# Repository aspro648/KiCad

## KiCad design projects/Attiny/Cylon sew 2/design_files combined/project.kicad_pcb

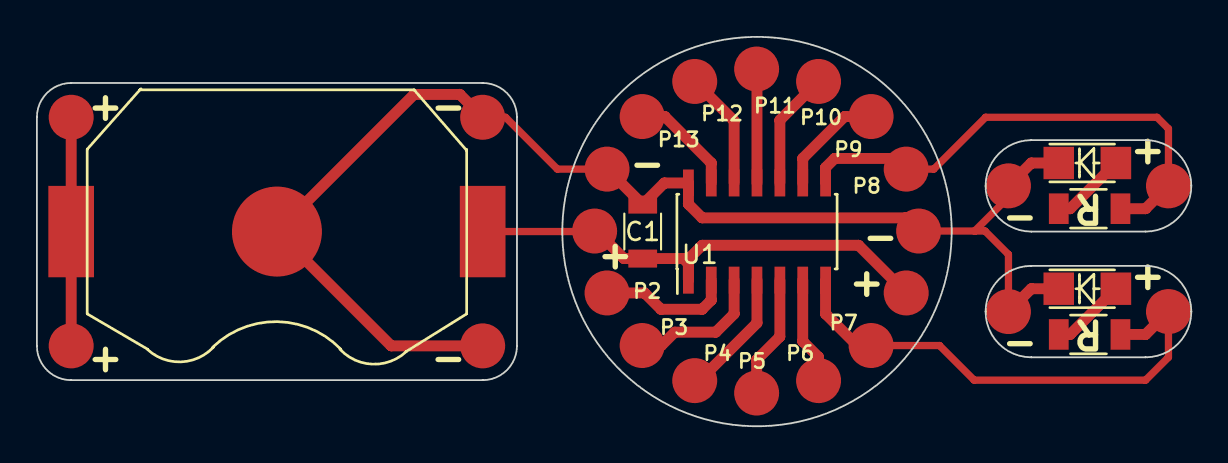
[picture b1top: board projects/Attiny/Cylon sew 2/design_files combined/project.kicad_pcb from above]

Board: 2 copper layers, 64.1 x 21.6 mm, 31 parts (0 on the bottom side), 16 nets.

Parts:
BT1: Battery; BATT_CR2032_SMD
C1: 0.1 uF; C_1206
D5, D5#2: LED; LED-1206
P1, P2, P3, P4, P5, P6, P7, P8, P8#2, P8#3, P9, P10, P11, P12, P13, P14, P14#2, P14#3: CONN_01X01; Pad
PG1, PG1#2, PG2: CONN_01X01; Pad
PP1, PP1#2, PP2: CONN_01X01; Pad
R5, R5#2: 100; R_1206
U1: ATTINY84A-SSU; SOIC-14_3.9x8.7mm_Pitch1.27mm

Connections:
+BATT: BT1.1, C1.1, P1.1, PP1.1, PP1#2.1, PP2.1, U1.1
/D0: P2.1, U1.2
/D1: P3.1, U1.3
/D2: P5.1, U1.5
/D3: P6.1, U1.6
/D4-MOSI: P7.1, P8#3.1, R5#2.1, U1.7
/D5-MISO: P8.1, P8#2.1, R5.1, U1.8
/D6-SCK: P9.1, U1.9
/D7: P10.1, U1.10
/D8: P11.1, U1.11
/D9: P12.1, U1.12
/D10: P13.1, U1.13
/RESET: P4.1, U1.4
GND: BT1.2, C1.2, D5.1, D5#2.1, P14.1, P14#2.1, P14#3.1, PG1.1, PG1#2.1, PG2.1, U1.14
unnamed: D5.2, R5.2
unnamed: D5#2.2, R5#2.2

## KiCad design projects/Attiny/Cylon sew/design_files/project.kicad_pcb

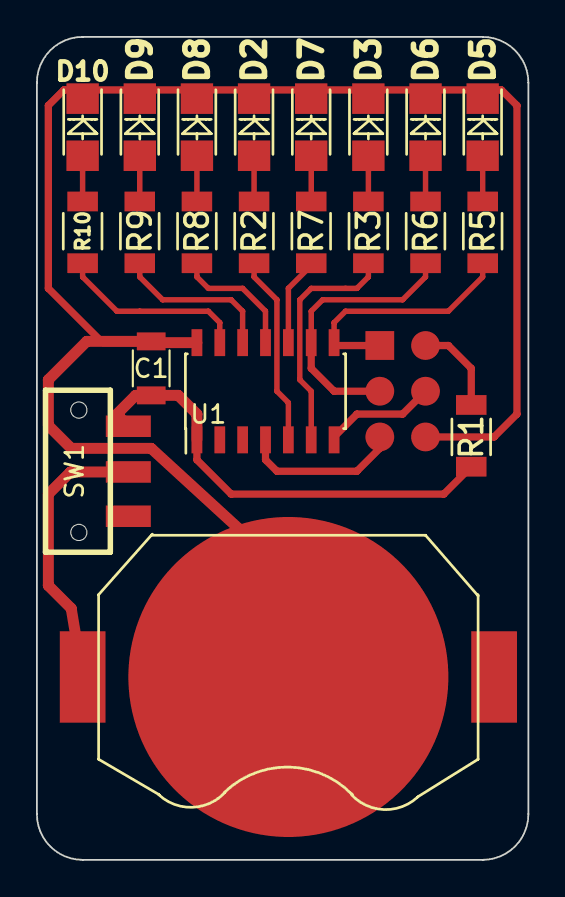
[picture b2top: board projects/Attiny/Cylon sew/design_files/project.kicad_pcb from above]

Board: 2 copper layers, 27.3 x 45.7 mm, 22 parts (0 on the bottom side), 22 nets.

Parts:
BT1: Battery; BATT_CR2032_SMD
C1: 0.1 uF; C_1206
CON1: AVR-ISP-6
D2, D3, D5, D6, D7, D8, D9, D10: LED; LED-1206
R1: 0; R_1206
R2, R3, R5, R6, R7, R8, R9, R10: 100; R_1206
SW1: SW_SPDT; SPST_SMD
U1: ATTINY84A-SSU; SOIC-14_3.9x8.7mm_Pitch1.27mm

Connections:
+BATT: C1.1, R1.2, SW1.3, U1.1
/D2: R2.1, U1.5
/D3: R3.1, U1.6
/D4-MOSI: CON1.4, U1.7
/D5-MISO: CON1.1, R5.1, U1.8
/D6-SCK: CON1.3, R6.1, U1.9
/D7: R7.1, U1.10
/D8: R8.1, U1.11
/D9: R9.1, U1.12
/D10: R10.1, U1.13
/RESET: CON1.5, U1.4
GND: BT1.2, C1.2, CON1.6, D2.1, D3.1, D5.1, D6.1, D7.1, D8.1, D9.1, D10.1, U1.14
unnamed: BT1.1, SW1.1
unnamed: CON1.2, R1.1
unnamed: D2.2, R2.2
unnamed: D3.2, R3.2
unnamed: D5.2, R5.2
unnamed: D6.2, R6.2
unnamed: D7.2, R7.2
unnamed: D8.2, R8.2
unnamed: D9.2, R9.2
unnamed: D10.2, R10.2

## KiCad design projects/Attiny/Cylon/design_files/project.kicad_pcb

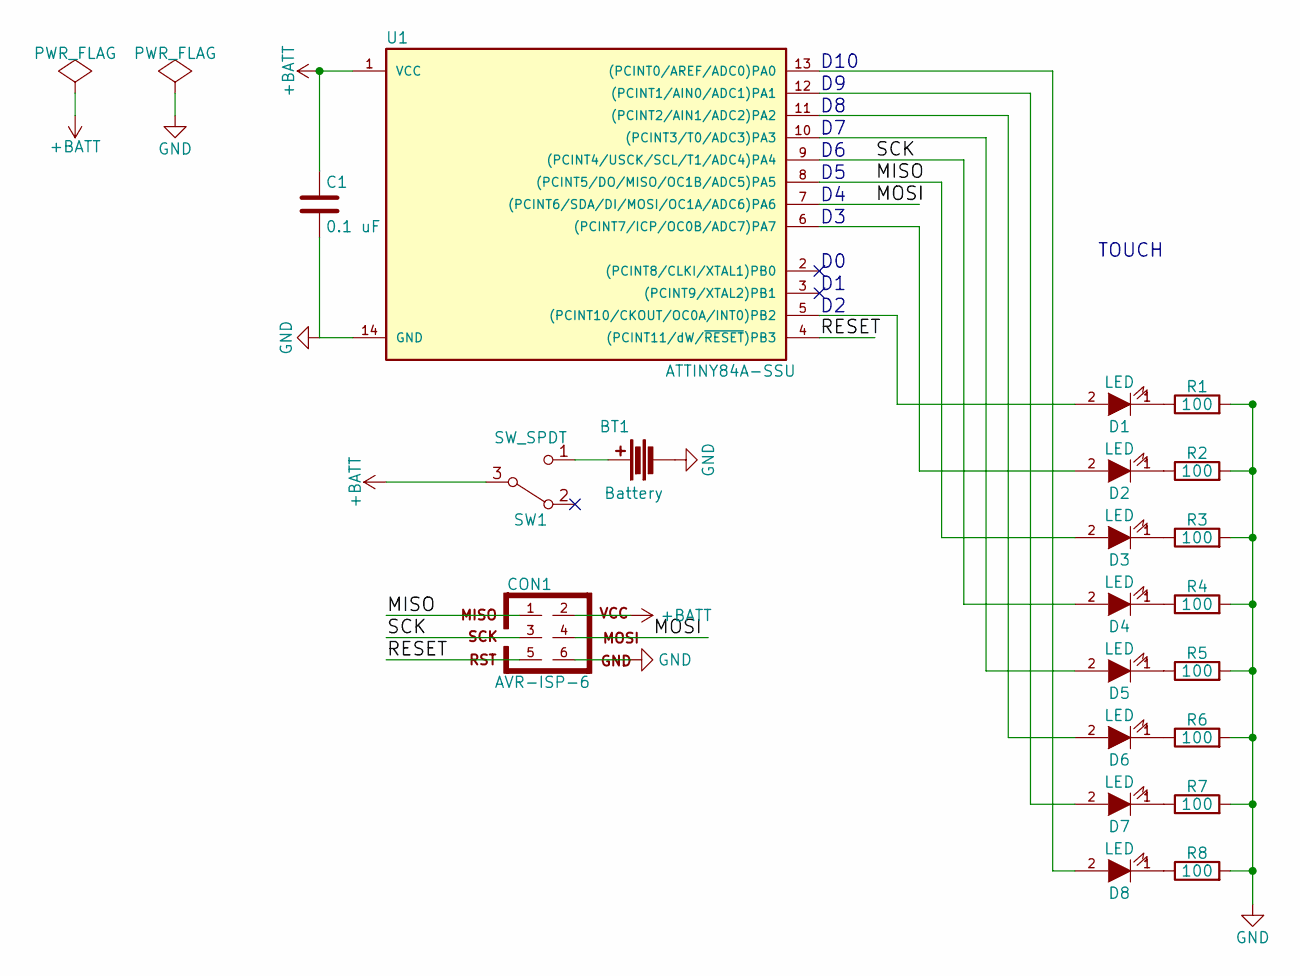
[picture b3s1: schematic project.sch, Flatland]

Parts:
BT1: Battery; BATT_Fliped
C1: 0.1 uF; C_0805_flip
CON1: AVR-ISP-6
D1, D2, D3, D4, D5, D6, D7, D8: LED; LED-0805_Flip
R1, R2, R3, R4, R5, R6, R7, R8: 100; R_0805_flip
SW1: SW_SPDT; SPST_Fliped
U1: ATTINY84A-SSU; SOIC-14_Flip

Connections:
+BATT: C1.1, CON1.2, SW1.3 (B), U1.1 (VCC)
/MISO: CON1.1, D3.2 (A), U1.8 ((PCINT5/DO/MISO/OC1B/ADC5)PA5)
/MOSI: CON1.4, U1.7 ((PCINT6/SDA/DI/MOSI/OC1A/ADC6)PA6)
/RESET: CON1.5, U1.4 ((PCINT11/dW/~RESET~)PB3)
/SCK: CON1.3, D4.2 (A), U1.9 ((PCINT4/USCK/SCL/T1/ADC4)PA4)
GND: BT1.2, C1.2, CON1.6, R1.2, R2.2, R3.2, R4.2, R5.2, R6.2, R7.2, R8.2, U1.14 (GND)
unnamed: BT1.1, SW1.1 (C)
unnamed: D1.1 (K), R1.1
unnamed: D1.2 (A), U1.5 ((PCINT10/CKOUT/OC0A/INT0)PB2)
unnamed: D2.1 (K), R2.1
unnamed: D2.2 (A), U1.6 ((PCINT7/ICP/OC0B/ADC7)PA7)
unnamed: D3.1 (K), R3.1
unnamed: D4.1 (K), R4.1
unnamed: D5.1 (K), R5.1
unnamed: D5.2 (A), U1.10 ((PCINT3/T0/ADC3)PA3)
unnamed: D6.1 (K), R6.1
unnamed: D6.2 (A), U1.11 ((PCINT2/AIN1/ADC2)PA2)
unnamed: D7.1 (K), R7.1
unnamed: D7.2 (A), U1.12 ((PCINT1/AIN0/ADC1)PA1)
unnamed: D8.1 (K), R8.1
unnamed: D8.2 (A), U1.13 ((PCINT0/AREF/ADC0)PA0)

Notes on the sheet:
D10
TOUCH

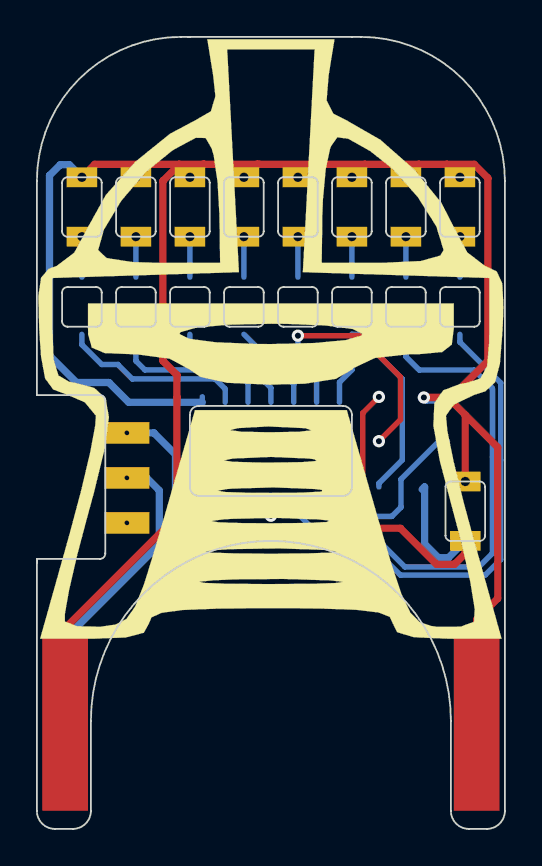
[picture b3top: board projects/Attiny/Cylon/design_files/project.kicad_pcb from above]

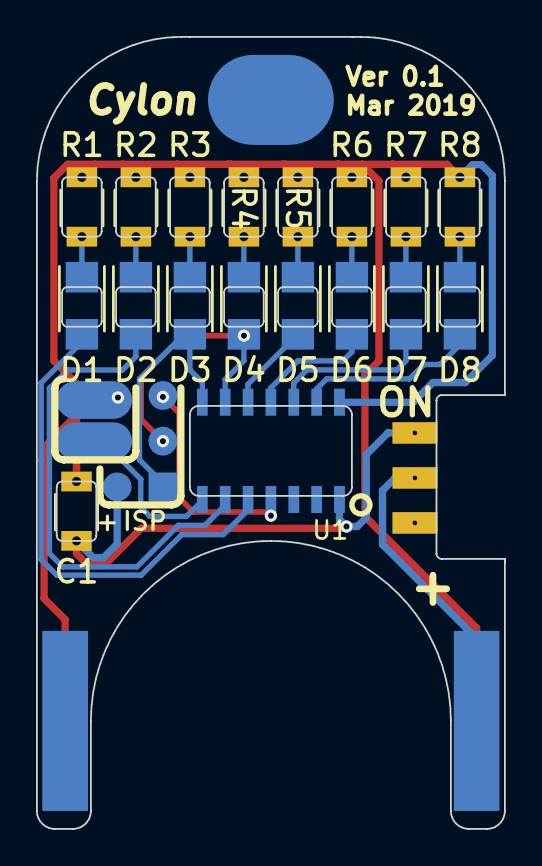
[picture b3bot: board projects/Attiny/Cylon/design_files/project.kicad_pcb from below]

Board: 2 copper layers, 26.0 x 44.0 mm, 22 parts (21 on the bottom side), 21 nets.

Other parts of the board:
P0: CONN_01X01; Pin_Header_Straight_1x01

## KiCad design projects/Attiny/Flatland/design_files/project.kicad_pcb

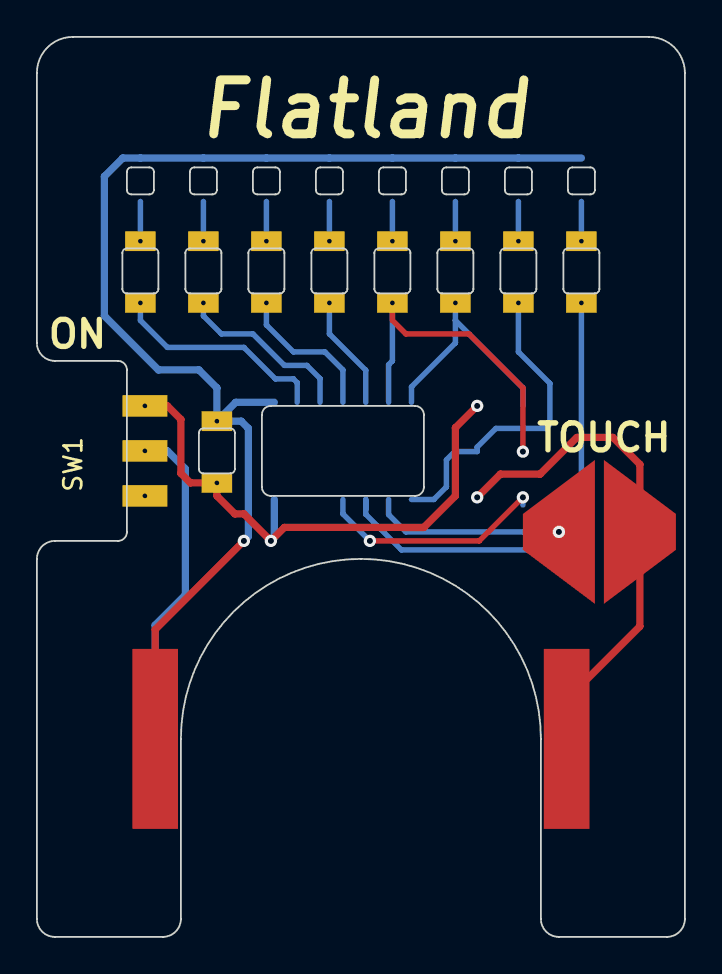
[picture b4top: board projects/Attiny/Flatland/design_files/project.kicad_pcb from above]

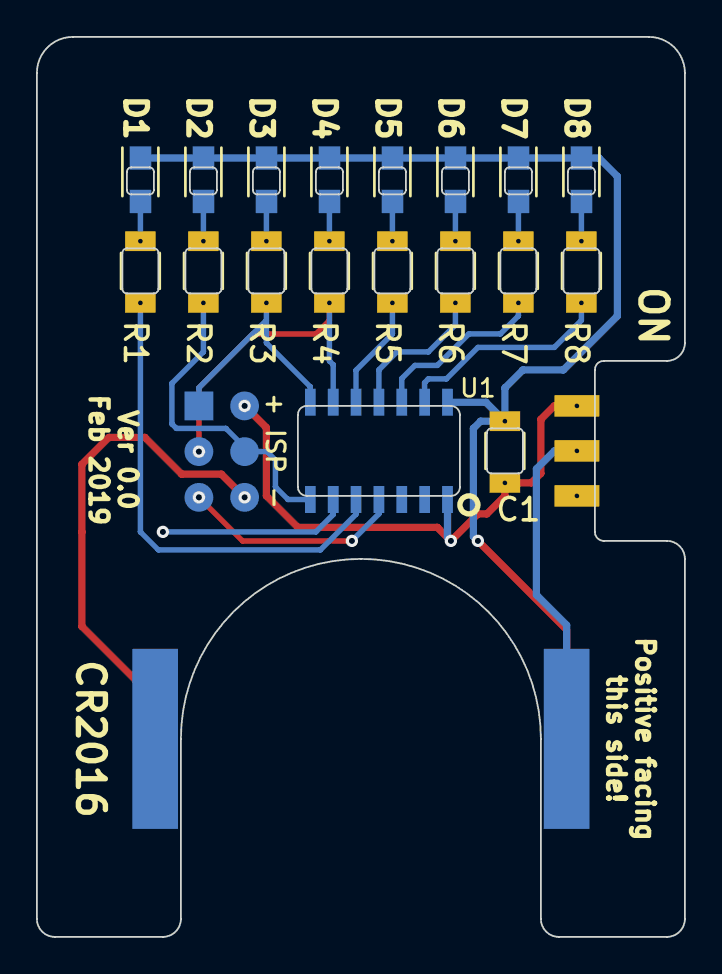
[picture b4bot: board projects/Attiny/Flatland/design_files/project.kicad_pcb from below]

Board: 2 copper layers, 36.0 x 50.0 mm, 22 parts (20 on the bottom side), 21 nets.

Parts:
BT1: Battery; BATT_Fliped
C1: 0.1 uF; C_0805_flip
CON1: AVR-ISP-6
D1, D2, D3, D4, D5, D6, D7, D8: LED; LED-0805_Flip
R1, R2, R3, R4, R5, R6, R7, R8: 100; R_0805_flip
SW1: SW_SPDT; SPST_Fliped
SW2: DNP; TOUCH
U1: ATTINY84A-SSU; SOIC-14_Flip

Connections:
+BATT: C1.1, CON1.2, SW1.3, U1.1
/MISO: CON1.1, R3.1, U1.8
/MOSI: CON1.4, R2.1, U1.7
/RESET: CON1.5, U1.4
/SCK: CON1.3, R4.1, U1.9
GND: BT1.2, C1.2, CON1.6, D1.1, D2.1, D3.1, D4.1, D5.1, D6.1, D7.1, D8.1, SW2.2, U1.14
unnamed: BT1.1, SW1.1
unnamed: D1.2, R1.2
unnamed: D2.2, R2.2
unnamed: D3.2, R3.2
unnamed: D4.2, R4.2
unnamed: D5.2, R5.2
unnamed: D6.2, R6.2
unnamed: D7.2, R7.2
unnamed: D8.2, R8.2
unnamed: R1.1, U1.5
unnamed: R5.1, U1.10
unnamed: R6.1, U1.11
unnamed: R7.1, U1.12
unnamed: R8.1, U1.13
unnamed: SW2.1, U1.6

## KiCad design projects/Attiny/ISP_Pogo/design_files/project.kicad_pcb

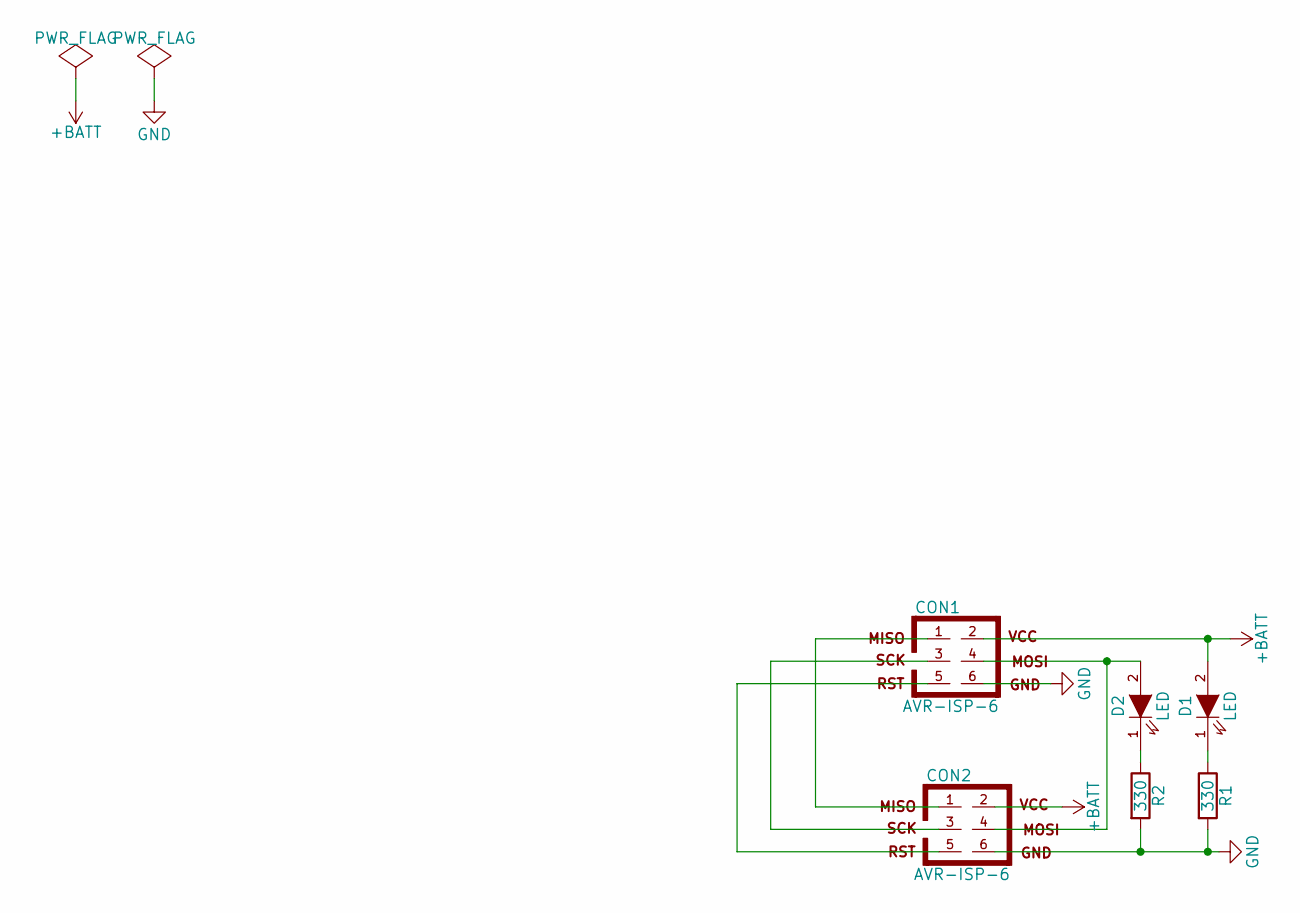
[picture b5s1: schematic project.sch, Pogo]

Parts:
CON1, CON2: AVR-ISP-6; Pin_Header_Straight_2x03_Pitch2.54mm
D1, D2: LED; LED_0805
R1, R2: 330; R_0805

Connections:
+BATT: CON1.2, CON2.2, D1.2 (A)
GND: CON1.6, CON2.6, R1.2, R2.2
unnamed: CON1.1, CON2.1
unnamed: CON1.3, CON2.3
unnamed: CON1.4, CON2.4, D2.2 (A)
unnamed: CON1.5, CON2.5
unnamed: D1.1 (K), R1.1
unnamed: D2.1 (K), R2.1

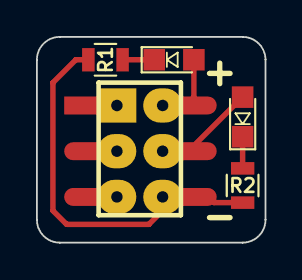
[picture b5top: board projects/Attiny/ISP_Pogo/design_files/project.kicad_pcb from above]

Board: 2 copper layers, 12.7 x 11.4 mm, 6 parts (0 on the bottom side), 8 nets.

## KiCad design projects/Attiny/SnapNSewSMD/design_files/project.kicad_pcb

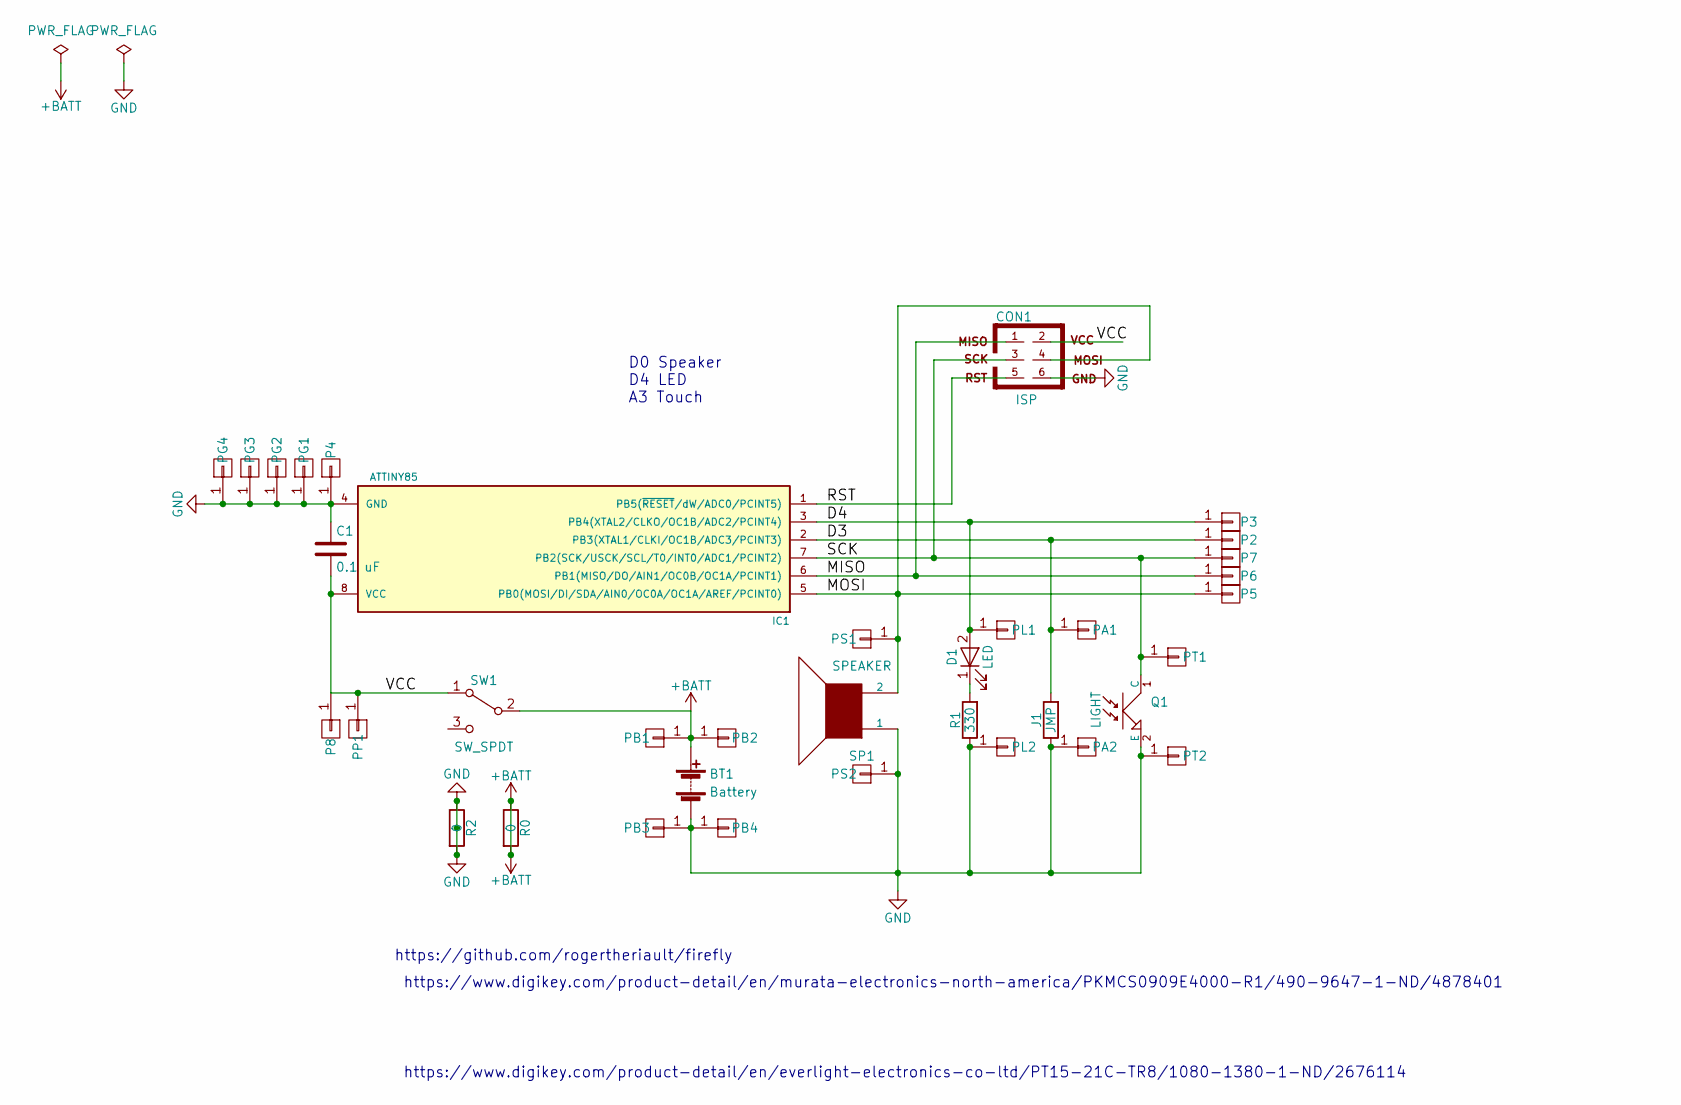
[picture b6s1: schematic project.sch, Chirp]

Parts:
BT1: Battery; BATT_CR2032_SMD
C1: 0.1 uF; C_1206
CON1: ISP; Pin_Header_Straight_2x03_Pitch2.54mm
D1: LED; LED_1206
IC1: ATTINY85; SOIJ-8_5.3x5.3mm_Pitch1.27mm
J1: JMP; R_1206_HandSoldering
P2, P3, P4, P5, P6, P7, P8: CONN_01X01; SolderWirePad_single_0-8mmDrill
PA1, PA2: CONN_01X01; SolderWirePad_single_0-8mmDrill
PB1, PB2, PB3, PB4: CONN_01X01; SolderWirePad_single_0-8mmDrill
PG1, PG2, PG3, PG4: CONN_01X01; SolderWirePad_single_0-8mmDrill
PL1, PL2: CONN_01X01; SolderWirePad_single_0-8mmDrill
PP1: CONN_01X01; SolderWirePad_single_0-8mmDrill
PS1, PS2: CONN_01X01; SolderWirePad_single_0-8mmDrill
PT1, PT2: CONN_01X01; SolderWirePad_single_0-8mmDrill
Q1: LIGHT; PhotoDiode_SMD-DIL2_4.5x4
R0, R2: 0; R_1206
R1: 330; R_1206
SP1: SPEAKER; PS1240_piezo
SW1: SW_SPDT

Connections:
+BATT: BT1.1 (+), PB1.1, PB2.1, R0.1, R0.2, SW1.2 (B)
/D3: IC1.2 (PB3(XTAL1/CLKI/OC1B/ADC3/PCINT3)), J1.2, P2.1, PA1.1
/D4: D1.2 (A), IC1.3 (PB4(XTAL2/CLKO/OC1B/ADC2/PCINT4)), P3.1, PL1.1
/MISO: CON1.1, IC1.6 (PB1(MISO/DO/AIN1/OC0B/OC1A/PCINT1)), P6.1
/MOSI: CON1.4, IC1.5 (PB0(MOSI/DI/SDA/AIN0/OC0A/OC1A/AREF/PCI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), P5.1, PS1.1, SP1.2
/RST: CON1.5, IC1.1 (PB5(~RESET~/dW/ADC0/PCINT5))
/SCK: CON1.3, IC1.7 (PB2(SCK/USCK/SCL/T0/INT0/ADC1/PCINT2)), P7.1, PT1.1, Q1.1 (C)
/VCC: C1.2, CON1.2, IC1.8 (VCC), P8.1, PP1.1, SW1.1 (A)
GND: BT1.2 (-), C1.1, CON1.6, IC1.4 (GND), J1.1, P4.1, PA2.1, PB3.1, PB4.1, PG1.1, PG2.1, PG3.1, PG4.1, PL2.1, PS2.1, PT2.1, Q1.2 (E), R1.1, R2.1, R2.2, SP1.1
unnamed: D1.1 (K), R1.2

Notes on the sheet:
D0 Speaker D4 LED A3 Touch
https://github.com/rogertheriault/firefly
https://www.digikey.com/product-detail/en/murata-electronics-north-america/PKMCS0909E4000-R1/490-9647-1-ND/4878401
https://www.digikey.com/product-detail/en/everlight-electronics-co-ltd/PT15-21C-TR8/1080-1380-1-ND/2676114

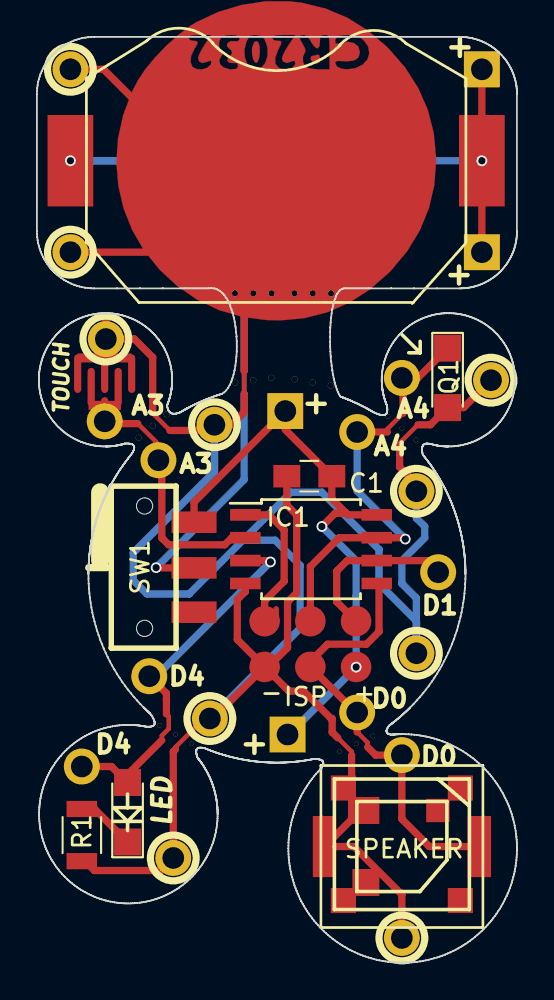
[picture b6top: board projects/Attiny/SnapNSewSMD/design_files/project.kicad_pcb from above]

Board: 2 copper layers, 26.7 x 51.4 mm, 35 parts (0 on the bottom side), 10 nets.

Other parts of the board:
VAL: MadeInOregonRev25
VAL#2: MB225rev
